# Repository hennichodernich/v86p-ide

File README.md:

# V86P 8-Bit IDE Controller

This is a variant of the XT-IDE ISA controller by [Glitch Works](http://www.glitchwrks.com/xt-ide) for Victor V86P 8086 laptops and compatibles.

This board is intended to be used with a custom BIOS like the XT-IDE Universal BIOS.

This design is based on [rev 4 of the Glitch Works XT-IDE](https://github.com/glitchwrks/xt_ide/tree/rev_4) using the information obtained by [MattinX](https://knm.org.uk/blog/2017/05/v86p-expansion/).

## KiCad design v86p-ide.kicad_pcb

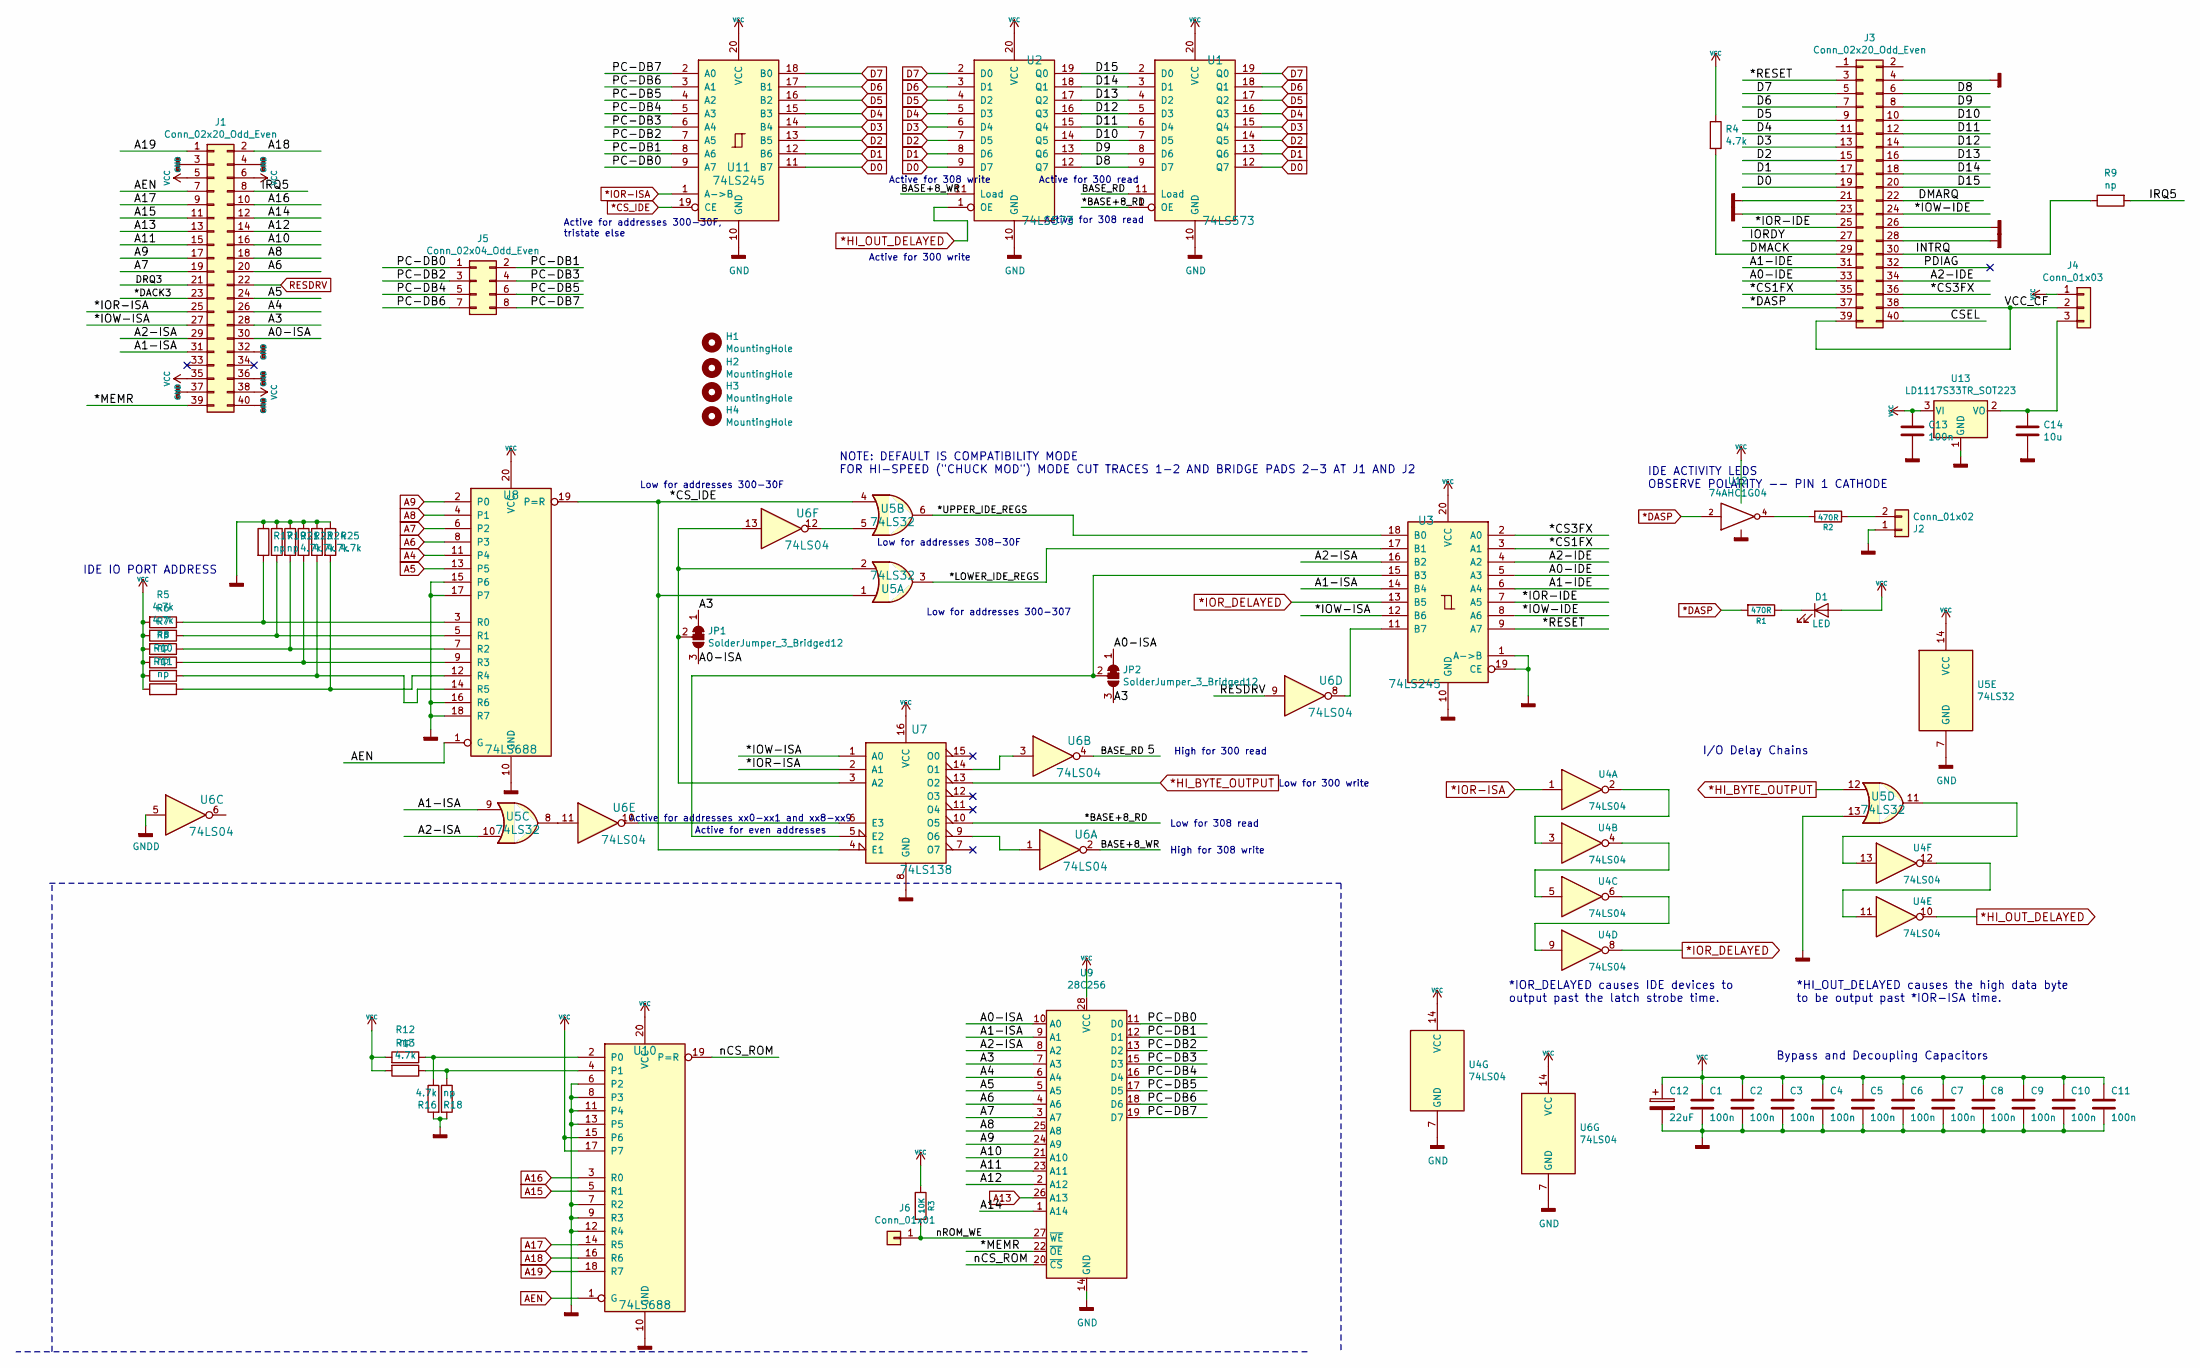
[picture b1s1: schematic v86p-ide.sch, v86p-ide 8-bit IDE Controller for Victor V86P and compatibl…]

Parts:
C1, C2, C3, C4, C5, C6, C7, C8, C9, C10, C11: 100n; C_0402_1005Metric
C12: 22uF; C_1206_3216Metric
C13: 100n; C_0603_1608Metric
C14: 10u; C_1206_3216Metric
D1: LED; LED_0603_1608Metric
H1, H2, H3, H4: MountingHole; MountingHole_3.2mm_M3_ISO7380
J1: Conn_02x20_Odd_Even; PinSocket_2x20_P2.54mm_Vertical
J2: Conn_01x02; PinHeader_1x02_P2.54mm_Horizontal
J3: Conn_02x20_Odd_Even; TE_4-1734839-0_1x40-1MP_P0.5mm_Horizontal
J4: Conn_01x03; PinHeader_1x03_P2.54mm_Horizontal
J5: Conn_02x04_Odd_Even; PinSocket_2x04_P2.54mm_Vertical
J6: Conn_01x01; PinHeader_1x01_P2.54mm_Horizontal
JP1, JP2: SolderJumper_3_Bridged12; SolderJumper-3_P1.3mm_Bridged12_RoundedPad1.0x1.5mm
R1, R2: 470R; R_0603_1608Metric
R3: 10K; R_0603_1608Metric
R4, R5, R6, R13, R16, R21, R23, R24, R25: 4.7k; R_0603_1608Metric
R7, R8, R9, R10, R11, R12, R17, R18, R19: np; R_0603_1608Metric
U1, U2: 74LS573; SOIC-20W_7.5x12.8mm_P1.27mm
U3, U11: 74LS245; SOIC-20W_7.5x12.8mm_P1.27mm
U4, U6: 74LS04; SOIC-14_3.9x8.7mm_P1.27mm
U5: 74LS32; SOIC-14_3.9x8.7mm_P1.27mm
U7: 74LS138; SOIC-16_3.9x9.9mm_P1.27mm
U8, U10: 74LS688; SOIC-20W_7.5x12.8mm_P1.27mm
U9: 28C256; DIP-28_W15.24mm_Socket
U12: 74AHC1G04; SOT-23-5
U13: LD1117S33TR_SOT223; SOT-223-3_TabPin2

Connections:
*CS_IDE: U5.1, U5.4, U7.4 (E1), U8.19 (P=R), U11.19 (CE)
*DASP: J3.37, R1.2, U12.2
*HI_BYTE_OUTPUT: U5.12, U7.13 (O2)
*HI_OUT_DELAYED: U2.1 (OE), U4.10
*IOR-ISA: J1.25, U4.1, U7.2 (A1), U11.1 (A->B)
*IOR_DELAYED: U3.13 (B5), U4.8
+5V: C1.1, C2.1, C3.1, C4.1, C5.1, C6.1, C7.1, C8.1, C9.1, C10.1, C11.1, C12.1, C13.1, D1.2 (A), J1.5, J1.6, J1.35, J1.38, J4.1, R3.1, R4.1, R5.2, R6.2, R7.2, R8.2, R10.2, R11.2, R12.2, R13.2, U1.20 (VCC), U2.20 (VCC), U3.20 (VCC), U4.14 (VCC), U5.14 (VCC), U6.14 (VCC), U7.16 (VCC), U8.20 (VCC), U9.28 (VCC), U10.15 (P6), U10.17 (P7), U10.20 (VCC), U11.20 (VCC), U12.3 (GND), U13.3 (VI)
/5: U1.11 (Load), U6.4
/*BASE+8_RD: U1.1 (OE), U7.10 (O5)
/*CS1FX: J3.35, U3.3 (A1)
/*CS3FX: J3.36, U3.2 (A0)
/*DACK3: J1.23
/*IOR-IDE: J3.25, U3.7 (A5)
/*IOW-IDE: J3.24, U3.8 (A6)
/*IOW-ISA: J1.27, U3.12 (B6), U7.1 (A0)
/*LOWER_IDE_REGS: U3.17 (B1), U5.3
/*MEMR: J1.39, U9.22 (~OE)
/*RESET: J3.3, U3.9 (A7)
/*UPPER_IDE_REGS: U3.18 (B0), U5.6
/A0-IDE: J3.33, U3.5 (A3)
/A0-ISA: J1.30, JP1.3 (B), JP2.1 (A), U9.10 (A0)
/A1-IDE: J3.31, U3.6 (A4)
/A1-ISA: J1.31, U3.14 (B4), U5.9, U9.9 (A1)
/A2-IDE: J3.34, U3.4 (A2)
/A2-ISA: J1.29, U3.16 (B2), U5.10, U9.8 (A2)
/A3: J1.28, JP1.1 (A), JP2.3 (B), U9.7 (A3)
/A10: J1.16, U9.21 (A10)
/A11: J1.15, U9.23 (A11)
/A12: J1.14, U9.2 (A12)
/A14: J1.12, U9.1 (A14)
/BASE+8_WR: U2.11 (Load), U6.2
/CSEL: J3.40
/D8: J3.6, U1.9 (D7), U2.12 (Q7)
/D9: J3.8, U1.8 (D6), U2.13 (Q6)
/D10: J3.10, U1.7 (D5), U2.14 (Q5)
/D11: J3.12, U1.6 (D4), U2.15 (Q4)
/D12: J3.14, U1.5 (D3), U2.16 (Q3)
/D13: J3.16, U1.4 (D2), U2.17 (Q2)
/D14: J3.18, U1.3 (D1), U2.18 (Q1)
/D15: J3.20, U1.2 (D0), U2.19 (Q0)
/DMACK: J3.29, R4.2
/DMARQ: J3.22
/DRQ3: J1.21
/INTRQ: J3.30, R9.1
/IORDY: J3.27
/IRQ5: J1.8, R9.2
/PC-DB0: J5.1, U9.11 (D0), U11.9 (A7)
/PC-DB1: J5.2, U9.12 (D1), U11.8 (A6)
/PC-DB2: J5.3, U9.13 (D2), U11.7 (A5)
/PC-DB3: J5.4, U9.15 (D3), U11.6 (A4)
/PC-DB4: J5.5, U9.16 (D4), U11.5 (A3)
/PC-DB5: J5.6, U9.17 (D5), U11.4 (A2)
/PC-DB6: J5.7, U9.18 (D6), U11.3 (A1)
/PC-DB7: J5.8, U9.19 (D7), U11.2 (A0)
/PDIAG: J3.32
/VCC_CF: J3.38, J3.39, J4.2
/nCS_ROM: U9.20 (~CS), U10.19 (P=R)
/nROM_WE: J6.1, R3.2, U9.27 (~WE)
A4: J1.26, U8.11 (P4), U9.6 (A4)
A5: J1.24, U8.13 (P5), U9.5 (A5)
A6: J1.20, U8.8 (P3), U9.4 (A6)
A7: J1.19, U8.6 (P2), U9.3 (A7)
A8: J1.18, U8.4 (P1), U9.25 (A8)
A9: J1.17, U8.2 (P0), U9.24 (A9)
A13: J1.13, U9.26 (A13)
A15: J1.11, U10.5 (R1)
A16: J1.10, U10.3 (R0)
A17: J1.9, U10.14 (R5)
A18: J1.2, U10.16 (R6)
A19: J1.1, U10.18 (R7)
AEN: J1.7, U8.1 (G), U10.1 (G)
D0: J3.19, U1.12 (Q7), U2.9 (D7), U11.11 (B7)
D1: J3.17, U1.13 (Q6), U2.8 (D6), U11.12 (B6)
D2: J3.15, U1.14 (Q5), U2.7 (D5), U11.13 (B5)
D3: J3.13, U1.15 (Q4), U2.6 (D4), U11.14 (B4)
D4: J3.11, U1.16 (Q3), U2.5 (D3), U11.15 (B3)
D5: J3.9, U1.17 (Q2), U2.4 (D2), U11.16 (B2)
D6: J3.7, U1.18 (Q1), U2.3 (D1), U11.17 (B1)
D7: J3.5, U1.19 (Q0), U2.2 (D0), U11.18 (B0)
unnamed: C14.1, J4.3, U13.2 (VO)
unnamed: D1.1 (K), R1.1
unnamed: J2.2, R2.1
unnamed: JP1.2 (C), U5.2, U6.13, U7.3 (A2)
unnamed: JP2.2 (C), U3.15 (B3), U7.5 (E2)
unnamed: R2.2, U12.4
unnamed: R10.1, R24.2, U8.14 (R5)
unnamed: R11.1, R25.2, U8.12 (R4)
unnamed: R12.1, R18.1, U10.2 (P0)
unnamed: R13.1, R16.1, U10.4 (P1)
unnamed: R5.1, R17.2, U8.3 (R0)
unnamed: R6.1, R19.2, U8.5 (R1)
unnamed: R7.1, R21.2, U8.7 (R2)
unnamed: R8.1, R23.2, U8.9 (R3)
unnamed: U3.11 (B7), U6.8
unnamed: U4.2, U4.3
unnamed: U4.4, U4.5
unnamed: U4.6, U4.9
unnamed: U4.11, U4.12
unnamed: U4.13, U5.11
unnamed: U5.5, U6.12
unnamed: U5.8, U6.11
unnamed: U6.1, U7.9 (O6)
unnamed: U6.3, U7.14 (O1)
unnamed: U6.10, U7.6 (E3)
RESDRV: J1.22, U6.9

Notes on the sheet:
IDE ACTIVITY LEDS OBSERVE POLARITY -- PIN 1 CATHODE
IDE IO PORT ADDRESS
NOTE: DEFAULT IS COMPATIBILITY MODE FOR HI-SPEED ("CHUCK MOD") MODE CUT TRACES 1-2 AND BRIDGE PADS 2-3 AT J1 AND J2
Bypass and Decoupling Capacitors
I/O Delay Chains
*IOR_DELAYED causes IDE devices to output past the latch strobe time.
*HI_OUT_DELAYED causes the high data byte to be output past *IOR-ISA time.
Low for addresses 300-30F
Low for addresses 300-307
Low for addresses 308-30F
Active for addresses xx0-xx1 and xx8-xx9
Active for even addresses
High for 300 read
Low for 300 write
Low for 308 read
High for 308 write
Active for 300 read
Active for 308 read
Active for 308 write
Active for 300 write
Active for addresses 300-30F, tristate else

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
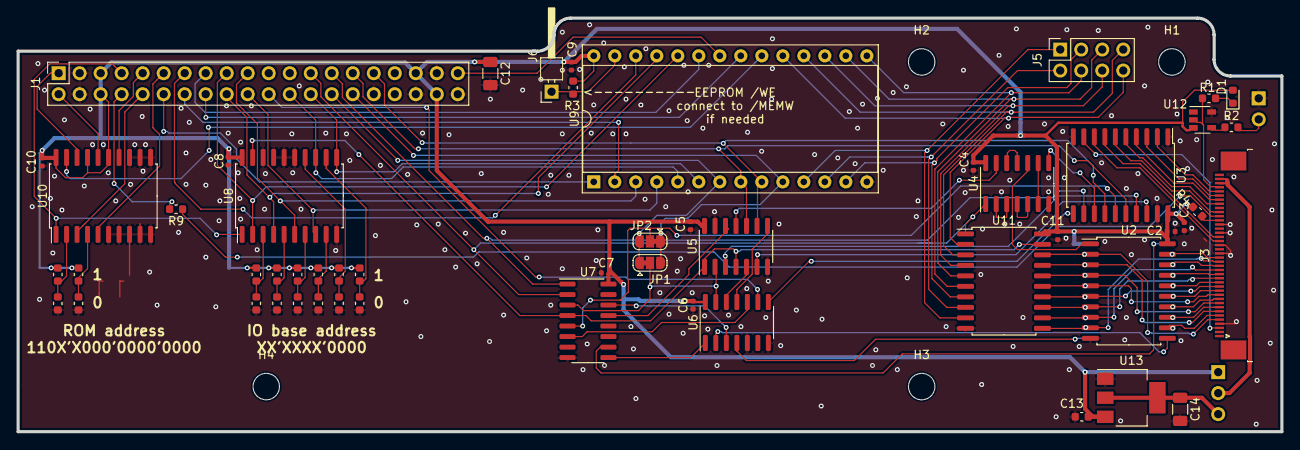
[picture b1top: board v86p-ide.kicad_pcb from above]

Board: 2 copper layers, 152.8 x 50.0 mm, 61 parts (0 on the bottom side), 100 nets.

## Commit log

2020-11-07 First public release.
2020-11-07 Fixed DRC errors

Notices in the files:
v86p-ide.kicad_pcb:
(c) 2020 hnch@gmx.net
